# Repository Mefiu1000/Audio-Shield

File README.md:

# Audio shield

The project is an audio shield for STM32 nucleo board or any other board compatible with arduino uno connectors. The board is generating analog audio signal in bandwidth up to 10 kHz. Sound output can be switched between headphones (mono) or speaker. Additionally keyboard with 8 switches is added to program special sounds etc. to generate.

## RC filter

To amplify a signal in desired bandwidth, a 4th order lowpass Chebyshev filter was used, because of its step roll-off characteristics. Filter was designed with a use of Texas Instruments Filter Design Tool:
https://webench.ti.com/filter-design-tool/filter-type

## Software

- KiCad v.8.0

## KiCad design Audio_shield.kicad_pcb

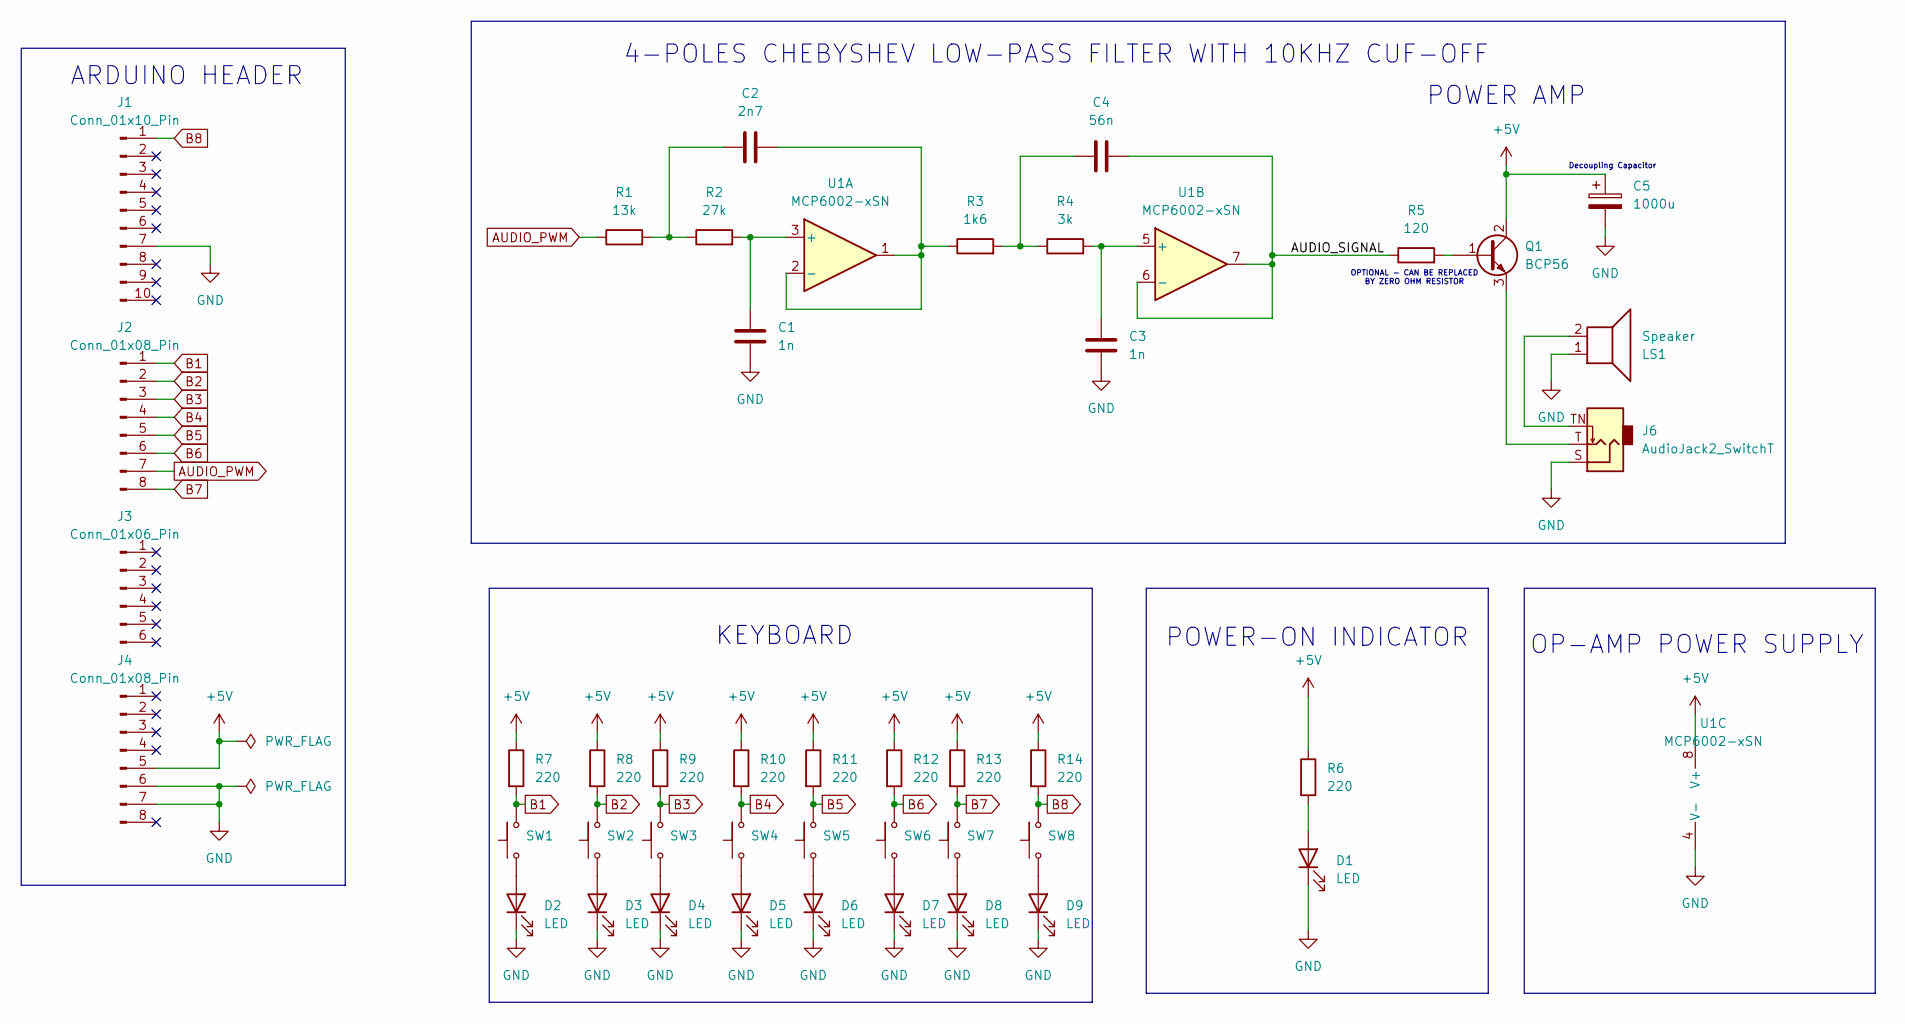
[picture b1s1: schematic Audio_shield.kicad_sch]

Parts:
C1, C3: 1n; C_0805_2012Metric_Pad1.18x1.45mm_HandSolder
C2: 2n7; C_0805_2012Metric_Pad1.18x1.45mm_HandSolder
C4: 56n; C_0805_2012Metric_Pad1.18x1.45mm_HandSolder
C5: 1000u; CP_Elec_8x10
D1, D2, D3, D4, D5, D6, D7, D8, D9: LED; LED_0805_2012Metric_Pad1.15x1.40mm_HandSolder
J1: Conn_01x10_Pin; PinHeader_1x10_P2.54mm_Vertical
J2, J4: Conn_01x08_Pin; PinHeader_1x08_P2.54mm_Vertical
J3: Conn_01x06_Pin; PinHeader_1x06_P2.54mm_Vertical
J6: AudioJack2_SwitchT; Jack_3.5mm_Cliff_FC68118_Horizontal
LS1: Speaker; TerminalBlock_Altech_AK300-2_P5.00mm
Q1: BCP56; SOT-223-3_TabPin2
R1: 13k; R_0805_2012Metric_Pad1.20x1.40mm_HandSolder
R2: 27k; R_0805_2012Metric_Pad1.20x1.40mm_HandSolder
R3: 1k6; R_0805_2012Metric_Pad1.20x1.40mm_HandSolder
R4: 3k; R_0805_2012Metric_Pad1.20x1.40mm_HandSolder
R5: 120; R_0805_2012Metric_Pad1.20x1.40mm_HandSolder
R6, R7, R8, R9, R10, R11, R12, R13, R14: 220; R_0805_2012Metric_Pad1.20x1.40mm_HandSolder
SW1, SW2, SW3, SW4, SW5, SW6, SW7, SW8: SW_PUSH_6mm_H5mm
U1: MCP6002-xSN; SOIC-8-1EP_3.9x4.9mm_P1.27mm_EP2.29x3mm

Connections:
+5V: C5.1, J4.5, Q1.2 (C), R6.1, R7.1, R8.1, R9.1, R10.1, R11.1, R12.1, R13.1, R14.1, U1.8 (V+)
/AUDIO_SIGNAL: C4.2, R5.1, U1.6 (-), U1.7
AUDIO_PWM: J2.7, R1.1
B1: J2.1, R7.2, SW1.2 (B)
B2: J2.2, R8.2, SW2.2 (B)
B3: J2.3, R9.2, SW3.2 (B)
B4: J2.4, R10.2, SW4.2 (B)
B5: J2.5, R11.2, SW5.2 (B)
B6: J2.6, R12.2, SW6.2 (B)
B7: J2.8, R13.2, SW7.2 (B)
B8: J1.1, R14.2, SW8.2 (B)
GND: C1.1, C3.1, C5.2, D1.1 (K), D2.1 (K), D3.1 (K), D4.1 (K), D5.1 (K), D6.1 (K), D7.1 (K), D8.1 (K), D9.1 (K), J1.7, J4.6, J4.7, J6.S, LS1.1, U1.4 (V-)
unnamed: C2.1, R1.2, R2.1
unnamed: C4.1, R3.2, R4.1
unnamed: D1.2 (A), R6.2
unnamed: D2.2 (A), SW1.1 (A)
unnamed: D3.2 (A), SW2.1 (A)
unnamed: D4.2 (A), SW3.1 (A)
unnamed: D5.2 (A), SW4.1 (A)
unnamed: D6.2 (A), SW5.1 (A)
unnamed: D7.2 (A), SW6.1 (A)
unnamed: D8.2 (A), SW7.1 (A)
unnamed: D9.2 (A), SW8.1 (A)
unnamed: J6.TN, LS1.2
unnamed: Q1.1 (B), R5.2
unnamed: J6.T, Q1.3 (E)
unnamed: C1.2, R2.2, U1.3 (+)
unnamed: C2.2, R3.1, U1.1, U1.2 (-)
unnamed: C3.2, R4.2, U1.5 (+)

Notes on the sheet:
4-POLES CHEBYSHEV LOW-PASS FILTER WITH 10KHZ CUF-OFF
OP-AMP POWER SUPPLY
Decoupling Capacitor
POWER AMP
OPTIONAL - CAN BE REPLACED BY ZERO OHM RESISTOR
ARDUINO HEADER
KEYBOARD
POWER-ON INDICATOR

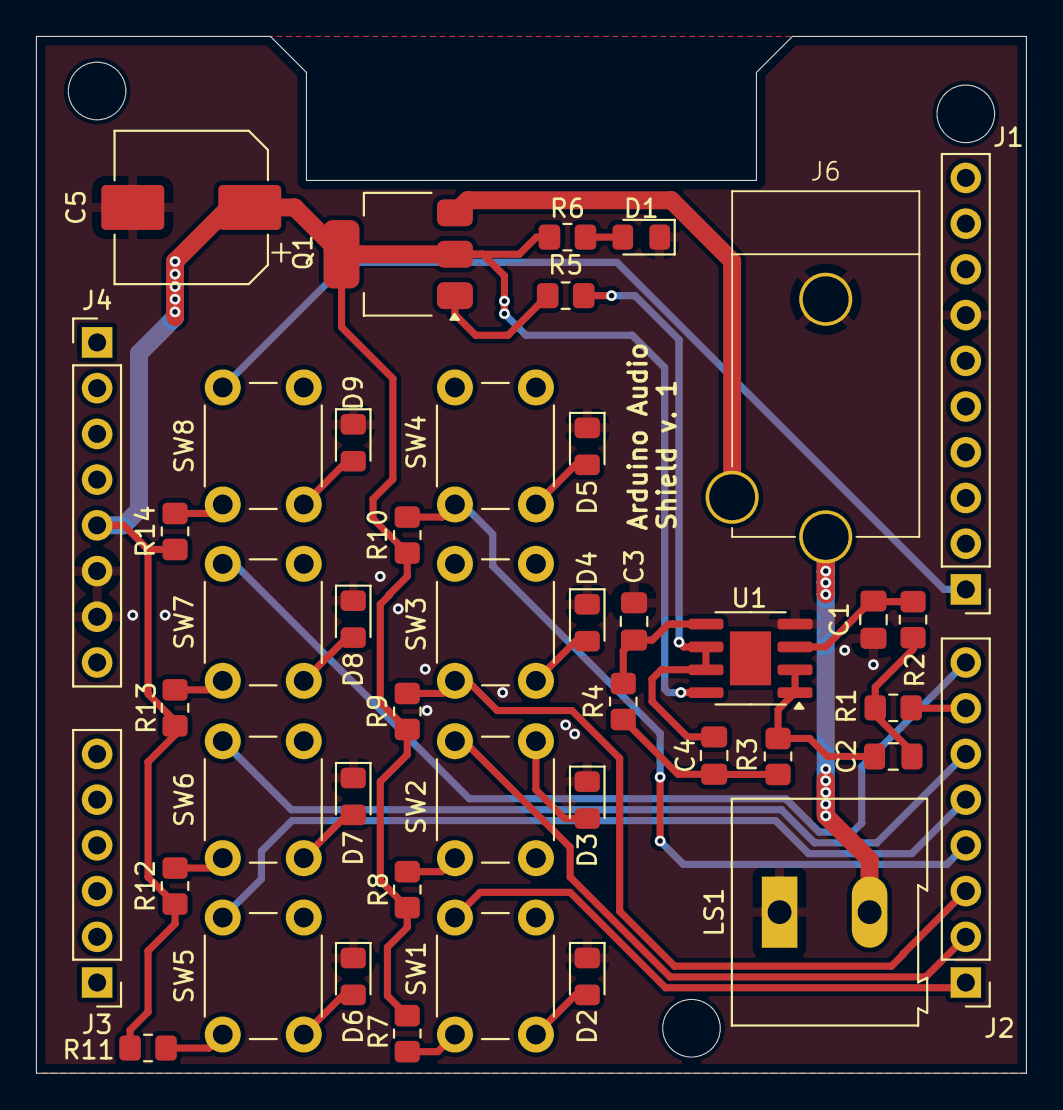
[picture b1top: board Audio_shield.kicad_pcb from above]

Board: 2 copper layers, 55.0 x 57.6 mm, 44 parts (0 on the bottom side), 29 nets.

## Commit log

2024-04-16 Add gitignore
2024-04-16 Add Schematics and PCB layout
